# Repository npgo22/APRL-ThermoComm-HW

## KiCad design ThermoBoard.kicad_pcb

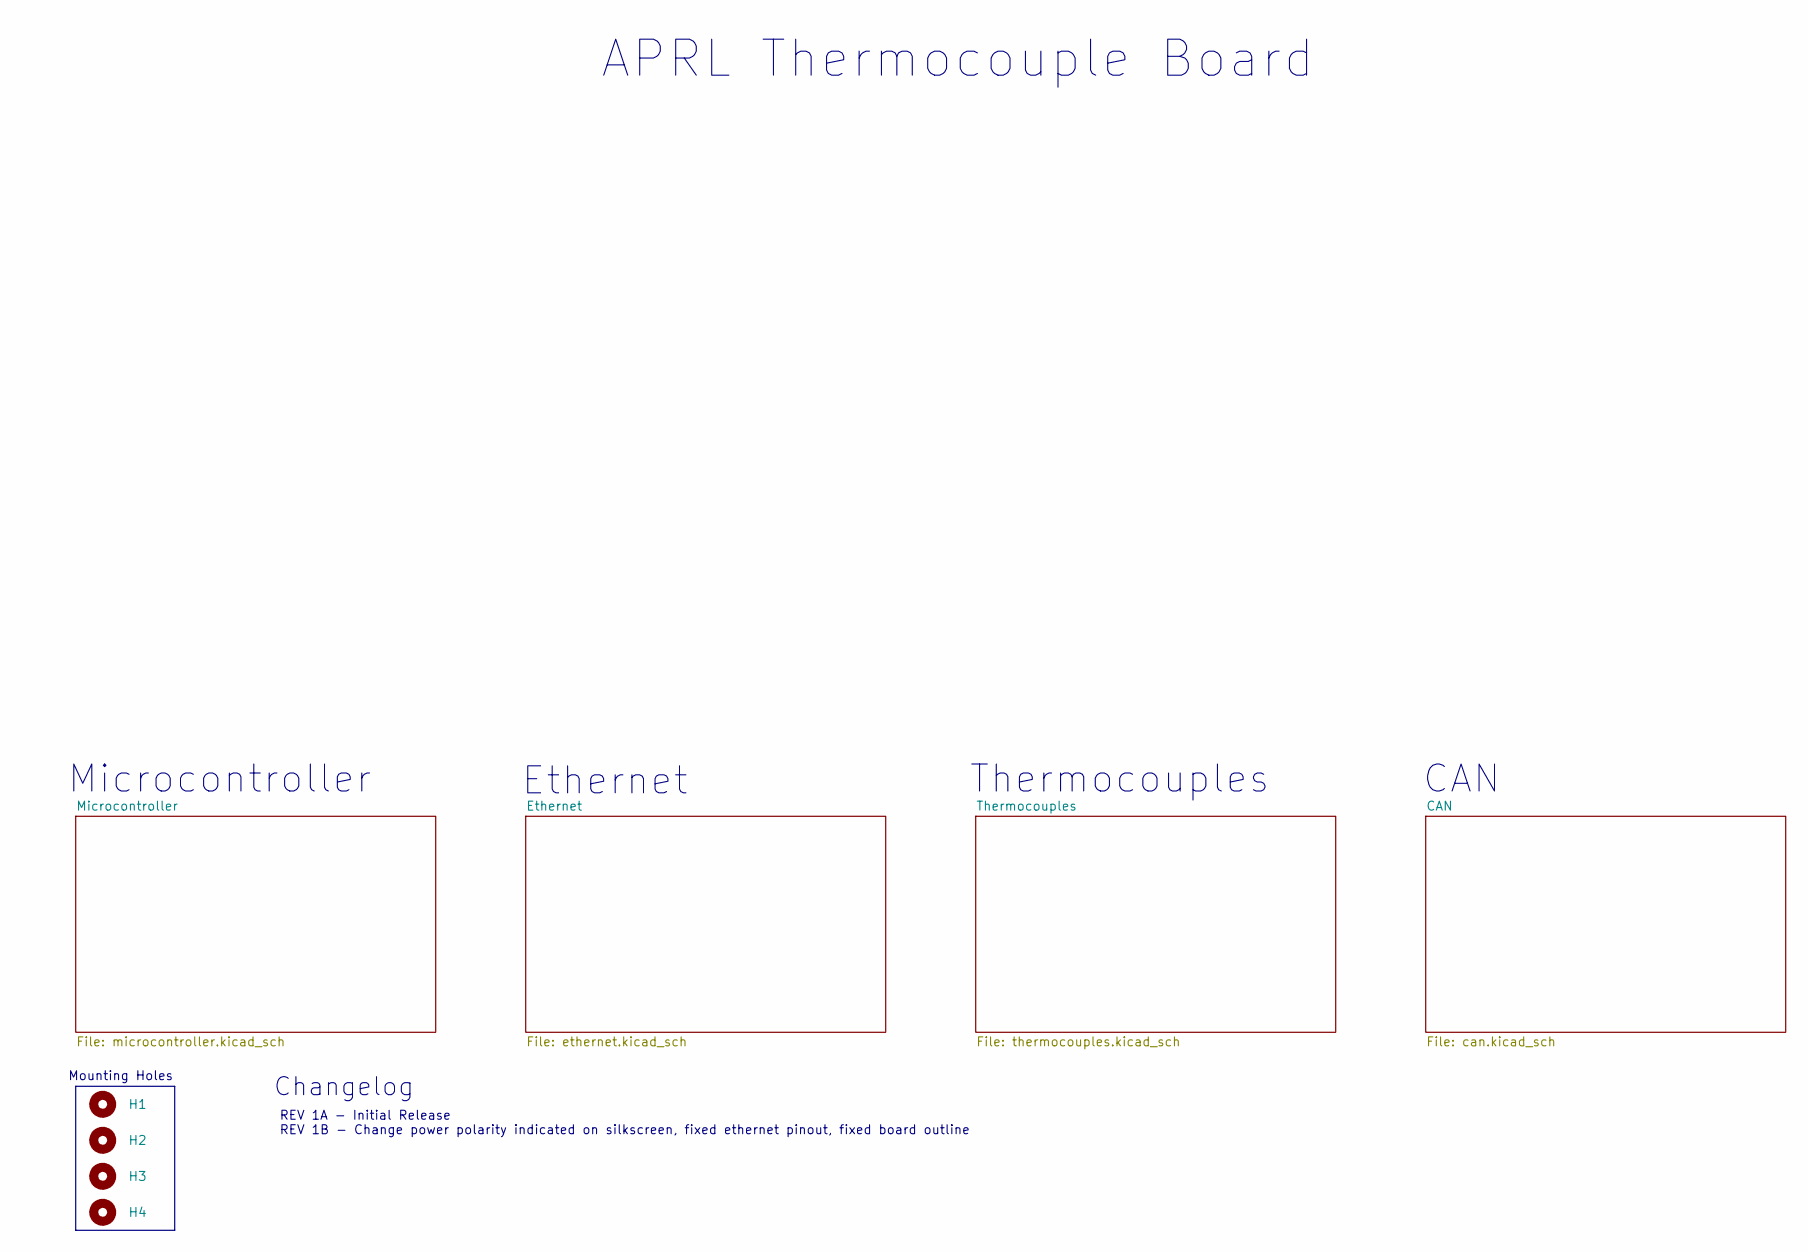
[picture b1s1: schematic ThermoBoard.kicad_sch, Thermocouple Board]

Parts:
H1, H2, H3, H4: MountingHole; MountingHole_3.2mm_M3

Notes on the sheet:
Changelog
APRL Thermocouple Board
REV 1A - Initial Release REV 1B - Change power polarity indicated on silkscreen, fixed ethernet pinout, fixed board outline
Mounting Holes
Thermocouples
Ethernet
Microcontroller
CAN

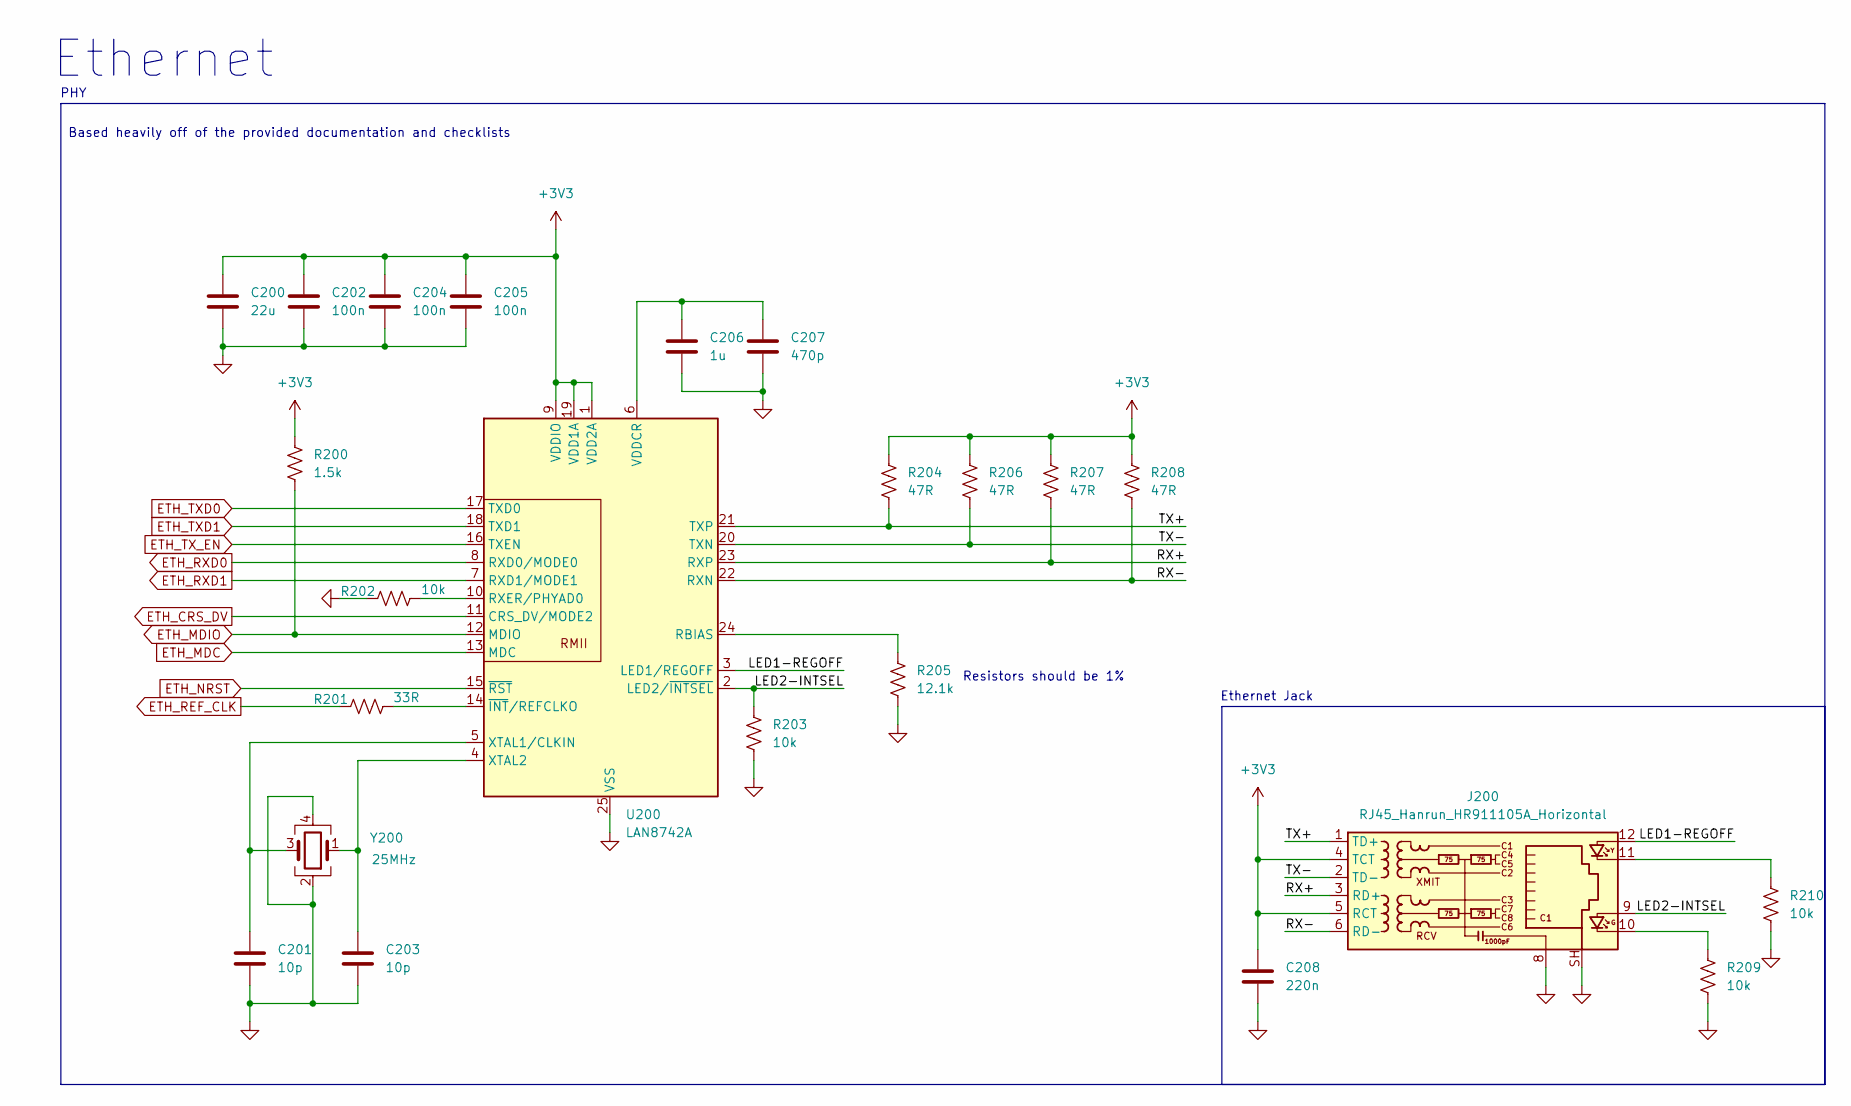
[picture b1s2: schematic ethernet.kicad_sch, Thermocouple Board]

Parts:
C200: 22u; C_0805_2012Metric; LCSC C602037
C201, C203: 10p; C_0402_1005Metric; LCSC C32949
C202, C204, C205: 100n; C_0402_1005Metric; LCSC C1525
C206: 1u; C_0402_1005Metric; LCSC C602037
C207: 470p; C_0402_1005Metric; LCSC C602037
C208: 220n; C_0402_1005Metric; LCSC C1525
J200: RJ45_Hanrun_HR911105A_Horizontal; LCSC C12074
R200: 1.5k; R_0402_1005Metric; LCSC C60490
R201: 33R; R_0402_1005Metric; LCSC C138002
R202, R203: 10k; R_0402_1005Metric; LCSC C60490
R204, R206, R207, R208: 47R; R_0402_1005Metric; LCSC C87044
R205: 12.1k; R_0402_1005Metric; LCSC C25852
R209, R210: 10k; R_0402_1005Metric; LCSC C105875
U200: LAN8742A; VQFN-24-1EP_4x4mm_P0.5mm_EP2.5x2.5mm_ThermalVias
Y200: 25MHz; CRYSTAL-SMD_4P-L2.0-W1.6-BL; LCSC C5765970

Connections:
+3V3: C200.1, C202.1, C204.1, C205.1, C208.1, J200.4 (TCT), J200.5 (RCT), R200.1, R204.1, R206.1, R207.1, R208.1, U200.1 (VDD2A), U200.9 (VDDIO), U200.19 (VDD1A); also elsewhere on the board
/Ethernet/LED1-REGOFF: J200.12, U200.3 (LED1/REGOFF)
/Ethernet/LED2-INTSEL: J200.9, R203.1, U200.2 (LED2/~INTSEL)
/Ethernet/RX+: J200.3 (RD+), R207.2, U200.23 (RXP)
/Ethernet/RX-: J200.6 (RD-), R208.2, U200.22 (RXN)
/Ethernet/TX+: J200.1 (TD+), R204.2, U200.21 (TXP)
/Ethernet/TX-: J200.2 (TD-), R206.2, U200.20 (TXN)
ETH_CRS_DV: U200.11 (CRS_DV/MODE2); also elsewhere on the board
ETH_MDC: U200.13 (MDC); also elsewhere on the board
ETH_MDIO: R200.2, U200.12 (MDIO); also elsewhere on the board
ETH_NRST: U200.15 (~RST); also elsewhere on the board
ETH_REF_CLK: R201.1; also elsewhere on the board
ETH_RXD0: U200.8 (RXD0/MODE0); also elsewhere on the board
ETH_RXD1: U200.7 (RXD1/MODE1); also elsewhere on the board
ETH_TXD0: U200.17 (TXD0); also elsewhere on the board
ETH_TXD1: U200.18 (TXD1); also elsewhere on the board
ETH_TX_EN: U200.16 (TXEN); also elsewhere on the board
GND: C200.2, C201.2, C202.2, C203.2, C204.2, C205.2, C206.2, C207.2, C208.2, J200.8, J200.SH, R202.1, R203.2, R205.2, R209.2, R210.2, U200.25 (VSS), Y200.2, Y200.4; also elsewhere on the board
unnamed: J200.10, R209.1
unnamed: J200.11, R210.1
unnamed: R205.1, U200.24 (RBIAS)
unnamed: R202.2, U200.10 (RXER/PHYAD0)
unnamed: C206.1, C207.1, U200.6 (VDDCR)
unnamed: C201.1, U200.5 (XTAL1/CLKIN), Y200.3
unnamed: C203.1, U200.4 (XTAL2), Y200.1
unnamed: R201.2, U200.14 (~INT/REFCLKO)

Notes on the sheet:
Ethernet
Resistors should be 1%
Ethernet Jack
PHY
Based heavily off of the provided documentation and checklists

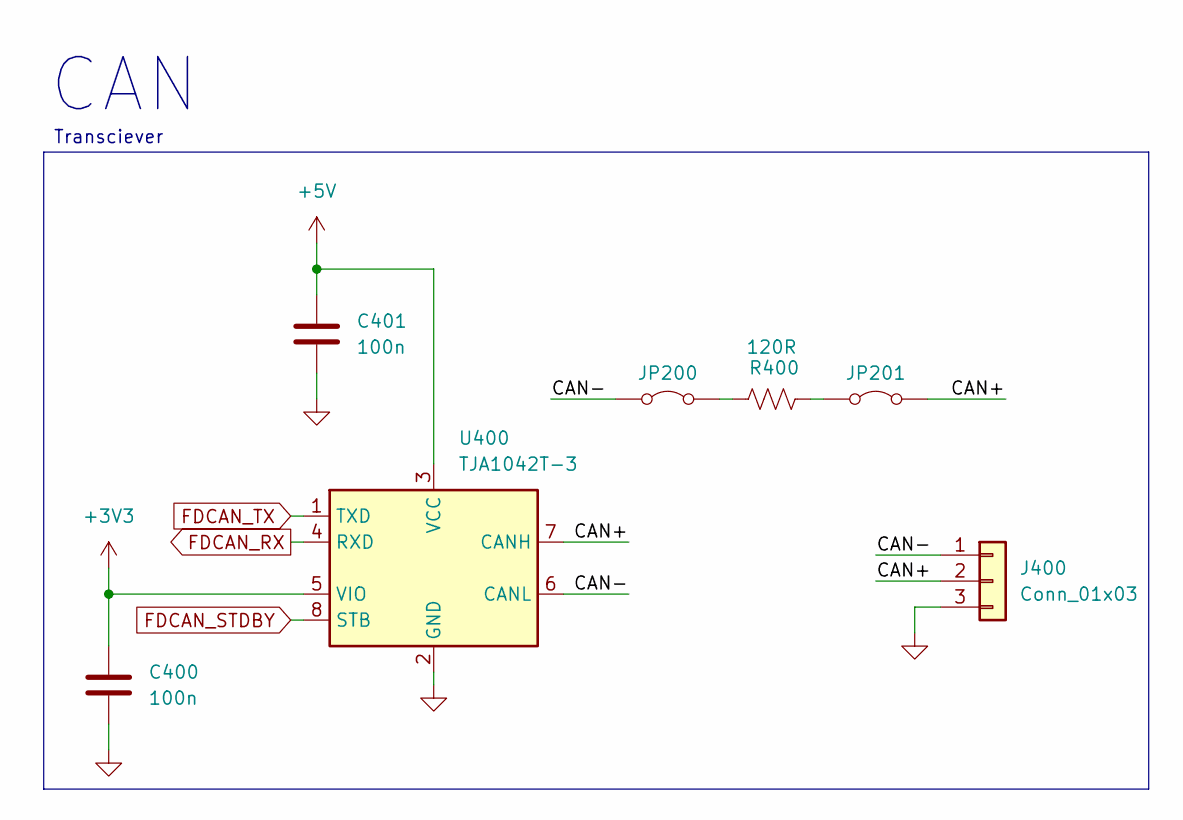
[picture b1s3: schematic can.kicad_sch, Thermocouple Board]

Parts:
C400, C401: 100n; C_0402_1005Metric; LCSC C1525
J400: Conn_01x03; PinHeader_1x03_P2.54mm_Vertical; LCSC C2337
JP200, JP201: Jumper_2_Bridged; PinHeader_1x02_P2.54mm_Vertical; LCSC C2337
R400: 120R; R_0402_1005Metric; LCSC C137954
U400: TJA1042T-3; SOIC-8_3.9x4.9mm_P1.27mm; LCSC C22445414

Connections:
+3V3: C400.1, U400.5 (VIO); also elsewhere on the board
+5V: C401.1, U400.3 (VCC); also elsewhere on the board
/CAN/CAN+: J400.2, JP201.2 (B), U400.7 (CANH)
/CAN/CAN-: J400.1, JP200.1 (A), U400.6 (CANL)
FDCAN_RX: U400.4 (RXD); also elsewhere on the board
FDCAN_STDBY: U400.8 (STB); also elsewhere on the board
FDCAN_TX: U400.1 (TXD); also elsewhere on the board
GND: C400.2, C401.2, J400.3, U400.2 (GND); also elsewhere on the board
unnamed: JP200.2 (B), R400.1
unnamed: JP201.1 (A), R400.2

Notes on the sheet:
CAN
Transciever

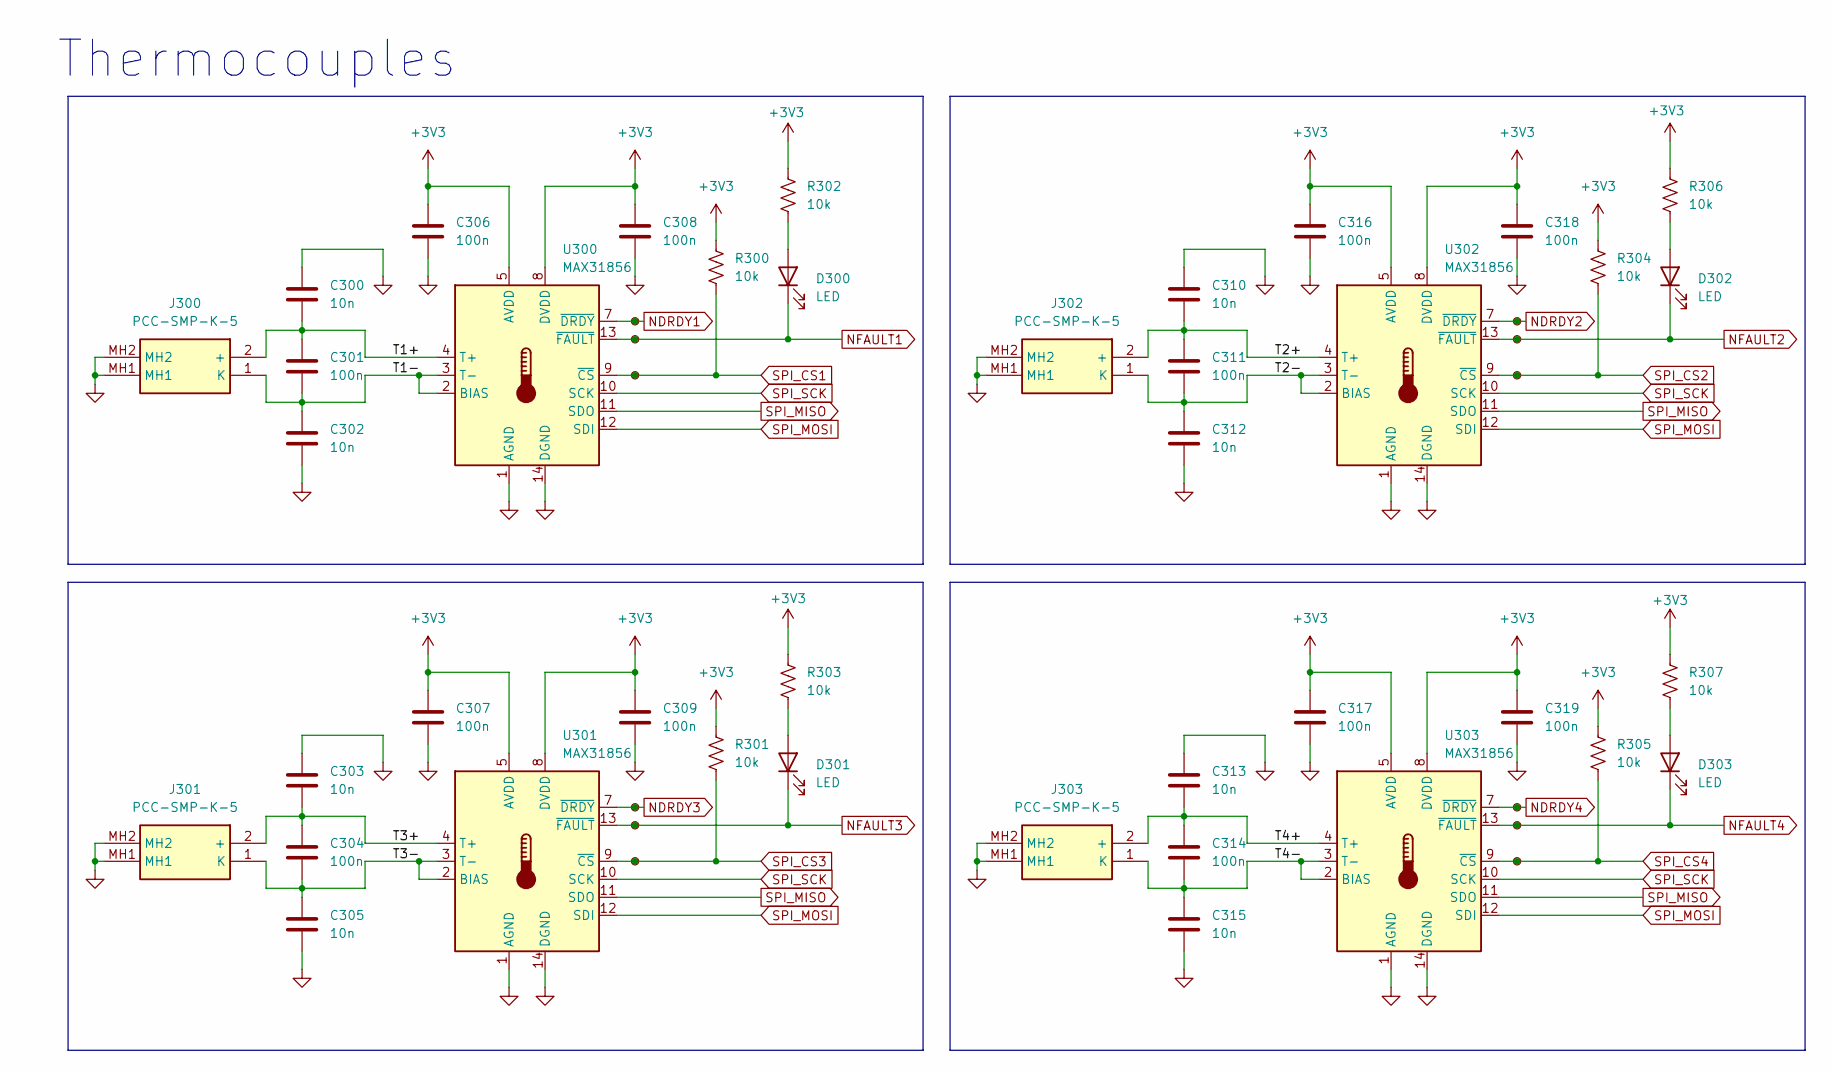
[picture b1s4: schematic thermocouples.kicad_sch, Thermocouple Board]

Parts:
C300, C302, C303, C305, C310, C312, C313, C315: 10n; C_0402_1005Metric; LCSC C15195
C301, C304, C306, C307, C308, C309, C311, C314, C316, C317, C318, C319: 100n; C_0402_1005Metric; LCSC C1525
D300, D301, D302, D303: LED; LED_0402_1005Metric; LCSC C21260817
J300, J301, J302, J303: PCC-SMP-K-5; PCCSMPK5; Manufacturer_Part_Number PCC-SMP-K-5
R300, R301, R304, R305: 10k; R_0402_1005Metric; LCSC C60490
R302, R303, R306, R307: 10k; R_0402_1005Metric; LCSC C105875
TP300, TP301, TP302, TP303, TP304, TP305, TP306, TP307, TP308, TP309, TP310, TP311: TestPoint_Small; TestPoint_Pad_D1.0mm
U300, U301, U302, U303: MAX31856; TSSOP-14_4.4x5mm_P0.65mm; LCSC C2653162

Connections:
+3V3: C306.1, C307.1, C308.1, C309.1, C316.1, C317.1, C318.1, C319.1, R300.1, R301.1, R302.1, R303.1, R304.1, R305.1, R306.1, R307.1, U300.5 (AVDD), U300.8 (DVDD), U301.5 (AVDD), U301.8 (DVDD), U302.5 (AVDD), U302.8 (DVDD), U303.5 (AVDD), U303.8 (DVDD); also elsewhere on the board
/Thermocouples/T1+: C300.2, C301.1, J300.2 (+), U300.4 (T+)
/Thermocouples/T1-: C301.2, C302.1, J300.1 (K), U300.2 (BIAS), U300.3 (T-)
/Thermocouples/T2+: C310.2, C311.1, J302.2 (+), U302.4 (T+)
/Thermocouples/T2-: C311.2, C312.1, J302.1 (K), U302.2 (BIAS), U302.3 (T-)
/Thermocouples/T3+: C303.2, C304.1, J301.2 (+), U301.4 (T+)
/Thermocouples/T3-: C304.2, C305.1, J301.1 (K), U301.2 (BIAS), U301.3 (T-)
/Thermocouples/T4+: C313.2, C314.1, J303.2 (+), U303.4 (T+)
/Thermocouples/T4-: C314.2, C315.1, J303.1 (K), U303.2 (BIAS), U303.3 (T-)
GND: C300.1, C302.2, C303.1, C305.2, C306.2, C307.2, C308.2, C309.2, C310.1, C312.2, C313.1, C315.2, C316.2, C317.2, C318.2, C319.2, J300.MH1, J300.MH2, J301.MH1, J301.MH2, J302.MH1, J302.MH2, J303.MH1, J303.MH2, U300.1 (AGND), U300.14 (DGND), U301.1 (AGND), U301.14 (DGND), U302.1 (AGND), U302.14 (DGND), U303.1 (AGND), U303.14 (DGND); also elsewhere on the board
NDRDY1: TP300.1, U300.7 (~DRDY); also elsewhere on the board
NDRDY2: TP306.1, U302.7 (~DRDY); also elsewhere on the board
NDRDY3: TP303.1, U301.7 (~DRDY); also elsewhere on the board
NDRDY4: TP309.1, U303.7 (~DRDY); also elsewhere on the board
NFAULT1: D300.1 (K), TP301.1, U300.13 (~FAULT); also elsewhere on the board
NFAULT2: D302.1 (K), TP307.1, U302.13 (~FAULT); also elsewhere on the board
NFAULT3: D301.1 (K), TP304.1, U301.13 (~FAULT); also elsewhere on the board
NFAULT4: D303.1 (K), TP310.1, U303.13 (~FAULT); also elsewhere on the board
unnamed: D300.2 (A), R302.2
unnamed: D301.2 (A), R303.2
unnamed: D302.2 (A), R306.2
unnamed: D303.2 (A), R307.2
SPI_CS1: R300.2, TP302.1, U300.9 (~CS); also elsewhere on the board
SPI_CS2: R304.2, TP308.1, U302.9 (~CS); also elsewhere on the board
SPI_CS3: R301.2, TP305.1, U301.9 (~CS); also elsewhere on the board
SPI_CS4: R305.2, TP311.1, U303.9 (~CS); also elsewhere on the board
SPI_MISO: U300.11 (SDO), U301.11 (SDO), U302.11 (SDO), U303.11 (SDO); also elsewhere on the board
SPI_MOSI: U300.12 (SDI), U301.12 (SDI), U302.12 (SDI), U303.12 (SDI); also elsewhere on the board
SPI_SCK: U300.10 (SCK), U301.10 (SCK), U302.10 (SCK), U303.10 (SCK); also elsewhere on the board

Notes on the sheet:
Thermocouples

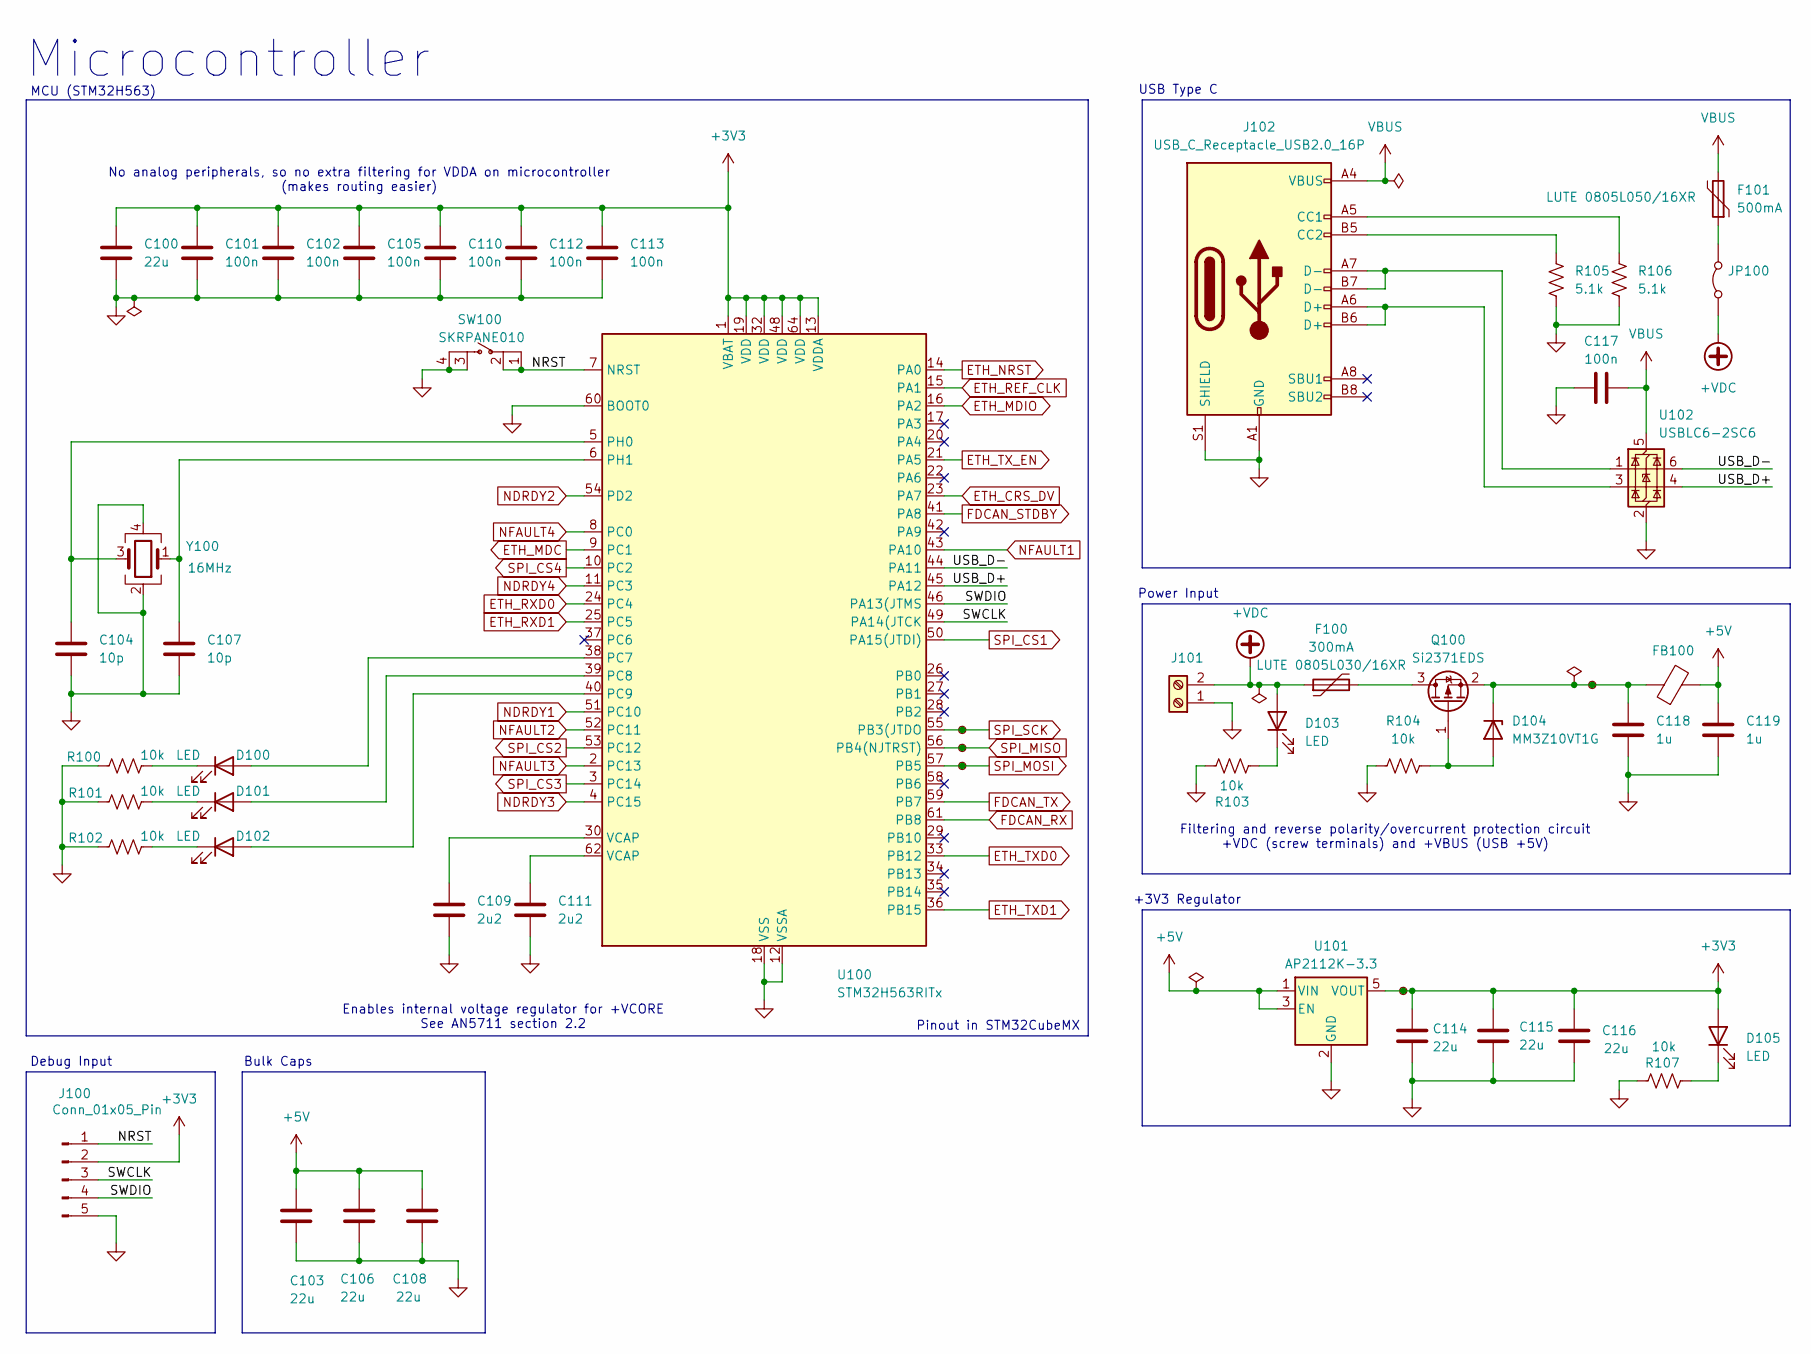
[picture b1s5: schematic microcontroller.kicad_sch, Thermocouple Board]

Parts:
C100, C103, C106, C108, C114, C115, C116: 22u; C_0805_2012Metric; LCSC C602037
C101, C102, C105, C110, C112, C113, C117: 100n; C_0402_1005Metric; LCSC C1525
C104, C107: 10p; C_0402_1005Metric; LCSC C32949
C109, C111: 2u2; C_0402_1005Metric; LCSC C170151
C118, C119: 1u; C_0402_1005Metric; LCSC C15849
D100, D101, D102, D103, D105: LED; LED_0402_1005Metric; LCSC C965793
D104: MM3Z10VT1G; SOD-323; LCSC C39057
F100: 300mA; Lute_16XR; Part LUTE 0805L030/16XR; LCSC C19193036
F101: 500mA; Lute_16XR; Part LUTE 0805L050/16XR; LCSC C22435898
FB100: FerriteBead; LSMGA160808T601RG
J100: Conn_01x05_Pin; PinHeader_1x05_P2.54mm_Vertical; LCSC C2337
J101: Screw_Terminal_01x02; TerminalBlock_Phoenix_MPT-0,5-2-2.54_1x02_P2.54mm_Horizontal; LCSC C3029316
J102: USB_C_Receptacle_USB2.0_16P; USB_C_Receptacle_HRO_TYPE-C-31-M-12; LCSC C165948
JP100: Jumper_2_Bridged; PinHeader_1x02_P2.54mm_Vertical; LCSC C2337
Q100: Si2371EDS; SOT-23; LCSC C467897
R100, R101, R102, R103, R107: 10k; R_0402_1005Metric; LCSC C105875
R104: 10k; R_0402_1005Metric; LCSC C60490
R105, R106: 5.1k; R_0402_1005Metric; LCSC C105873
SW100: SKRPANE010; SW-SMD_4P-L4.2-W3.2-P2.15-LS4.6-2; LCSC C2909692
TP100, TP101, TP102, TP104, TP105: TestPoint_Small; TestPoint_Pad_D1.0mm
U100: STM32H563RITx; LQFP-64_10x10mm_P0.5mm; LCSC C20619634
U101: AP2112K-3.3; SOT-23-5; LCSC C51118
U102: USBLC6-2SC6; SOT-23-6; LCSC C7519
Y100: 16MHz; CRYSTAL-SMD_4P-L2.0-W1.6-BL; LCSC C2901668

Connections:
+3V3: C100.1, C101.1, C102.1, C105.1, C110.1, C112.1, C113.1, C114.2, C115.2, C116.2, D105.2 (A), J100.2, TP104.1, U100.1 (VBAT), U100.13 (VDDA), U100.19 (VDD), U100.32 (VDD), U100.48 (VDD), U100.64 (VDD), U101.5 (VOUT); also elsewhere on the board
+5V: C103.2, C106.2, C108.2, C119.1, FB100.2, U101.1 (VIN), U101.3 (EN); also elsewhere on the board
+VDC: D103.2 (A), F100.1, J101.2, JP100.1 (A)
/Microcontroller/NRST: J100.1, SW100.1, SW100.2, U100.7 (NRST)
/Microcontroller/SWCLK: J100.3, U100.49 (PA14(JTCK)
/Microcontroller/SWDIO: J100.4, U100.46 (PA13(JTMS)
/Microcontroller/USB_D+: U100.45 (PA12), U102.4 (I/O2)
/Microcontroller/USB_D-: U100.44 (PA11), U102.6 (I/O1)
ETH_CRS_DV: U100.23 (PA7); also elsewhere on the board
ETH_MDC: U100.9 (PC1); also elsewhere on the board
ETH_MDIO: U100.16 (PA2); also elsewhere on the board
ETH_NRST: U100.14 (PA0); also elsewhere on the board
ETH_REF_CLK: U100.15 (PA1); also elsewhere on the board
ETH_RXD0: U100.24 (PC4); also elsewhere on the board
ETH_RXD1: U100.25 (PC5); also elsewhere on the board
ETH_TXD0: U100.33 (PB12); also elsewhere on the board
ETH_TXD1: U100.36 (PB15); also elsewhere on the board
ETH_TX_EN: U100.21 (PA5); also elsewhere on the board
FDCAN_RX: U100.61 (PB8); also elsewhere on the board
FDCAN_STDBY: U100.41 (PA8); also elsewhere on the board
FDCAN_TX: U100.59 (PB7); also elsewhere on the board
GND: C100.2, C101.2, C102.2, C103.1, C104.2, C105.2, C106.1, C107.2, C108.1, C109.2, C110.2, C111.2, C112.2, C113.2, C114.1, C115.1, C116.1, C117.1, C118.2, C119.2, J100.5, J101.1, J102.A1 (GND), J102.A12 (GND), J102.B1 (GND), J102.B12 (GND), J102.S1 (SHIELD), R100.1, R101.1, R102.1, R103.2, R104.1, R105.2, R106.2, R107.1, SW100.3, SW100.4, U100.12 (VSSA), U100.18 (VSS), U100.31 (VSS), U100.47 (VSS), U100.60 (BOOT0), U100.63 (VSS), U101.2 (GND), U102.2 (GND), Y100.2, Y100.4; also elsewhere on the board
NDRDY1: U100.51 (PC10); also elsewhere on the board
NDRDY2: U100.54 (PD2); also elsewhere on the board
NDRDY3: U100.4 (PC15); also elsewhere on the board
NDRDY4: U100.11 (PC3); also elsewhere on the board
NFAULT1: U100.43 (PA10); also elsewhere on the board
NFAULT2: U100.52 (PC11); also elsewhere on the board
NFAULT3: U100.2 (PC13); also elsewhere on the board
NFAULT4: U100.8 (PC0); also elsewhere on the board
unnamed: C109.1, U100.30 (VCAP)
unnamed: C111.1, U100.62 (VCAP)
unnamed: D100.2 (A), U100.38 (PC7)
unnamed: D100.1 (K), R100.2
unnamed: D101.2 (A), U100.39 (PC8)
unnamed: D101.1 (K), R101.2
unnamed: D102.2 (A), U100.40 (PC9)
unnamed: D102.1 (K), R102.2
unnamed: D103.1 (K), R103.1
unnamed: D104.2 (A), Q100.1 (G), R104.2
unnamed: C118.1, D104.1 (K), FB100.1, Q100.2 (S), TP105.1
unnamed: D105.1 (K), R107.2
unnamed: J102.A5 (CC1), R106.1
unnamed: J102.B5 (CC2), R105.1
unnamed: J102.A6 (D+), J102.B6 (D+), U102.3 (I/O2)
unnamed: J102.A7 (D-), J102.B7 (D-), U102.1 (I/O1)
unnamed: F101.1, JP100.2 (B)
unnamed: F100.2, Q100.3 (D)
unnamed: C104.1, U100.5 (PH0), Y100.3
unnamed: C107.1, U100.6 (PH1), Y100.1
SPI_CS1: U100.50 (PA15(JTDI)); also elsewhere on the board
SPI_CS2: U100.53 (PC12); also elsewhere on the board
SPI_CS3: U100.3 (PC14); also elsewhere on the board
SPI_CS4: U100.10 (PC2); also elsewhere on the board
SPI_MISO: TP101.1, U100.56 (PB4(NJTRST)); also elsewhere on the board
SPI_MOSI: TP102.1, U100.57 (PB5); also elsewhere on the board
SPI_SCK: TP100.1, U100.55 (PB3(JTDO); also elsewhere on the board
VBUS: C117.2, F101.2, J102.A4 (VBUS), J102.A9 (VBUS), J102.B4 (VBUS), J102.B9 (VBUS), U102.5 (VBUS)

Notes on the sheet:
Microcontroller
Debug Input
Power Input
+3V3 Regulator
Pinout in STM32CubeMX
Enables internal voltage regulator for +VCORE See AN5711 section 2.2
No analog peripherals, so no extra filtering for VDDA on microcontroller (makes routing easier)
Bulk Caps
Filtering and reverse polarity/overcurrent protection circuit +VDC (screw terminals) and +VBUS (USB +5V)
USB Type C
MCU (STM32H563)

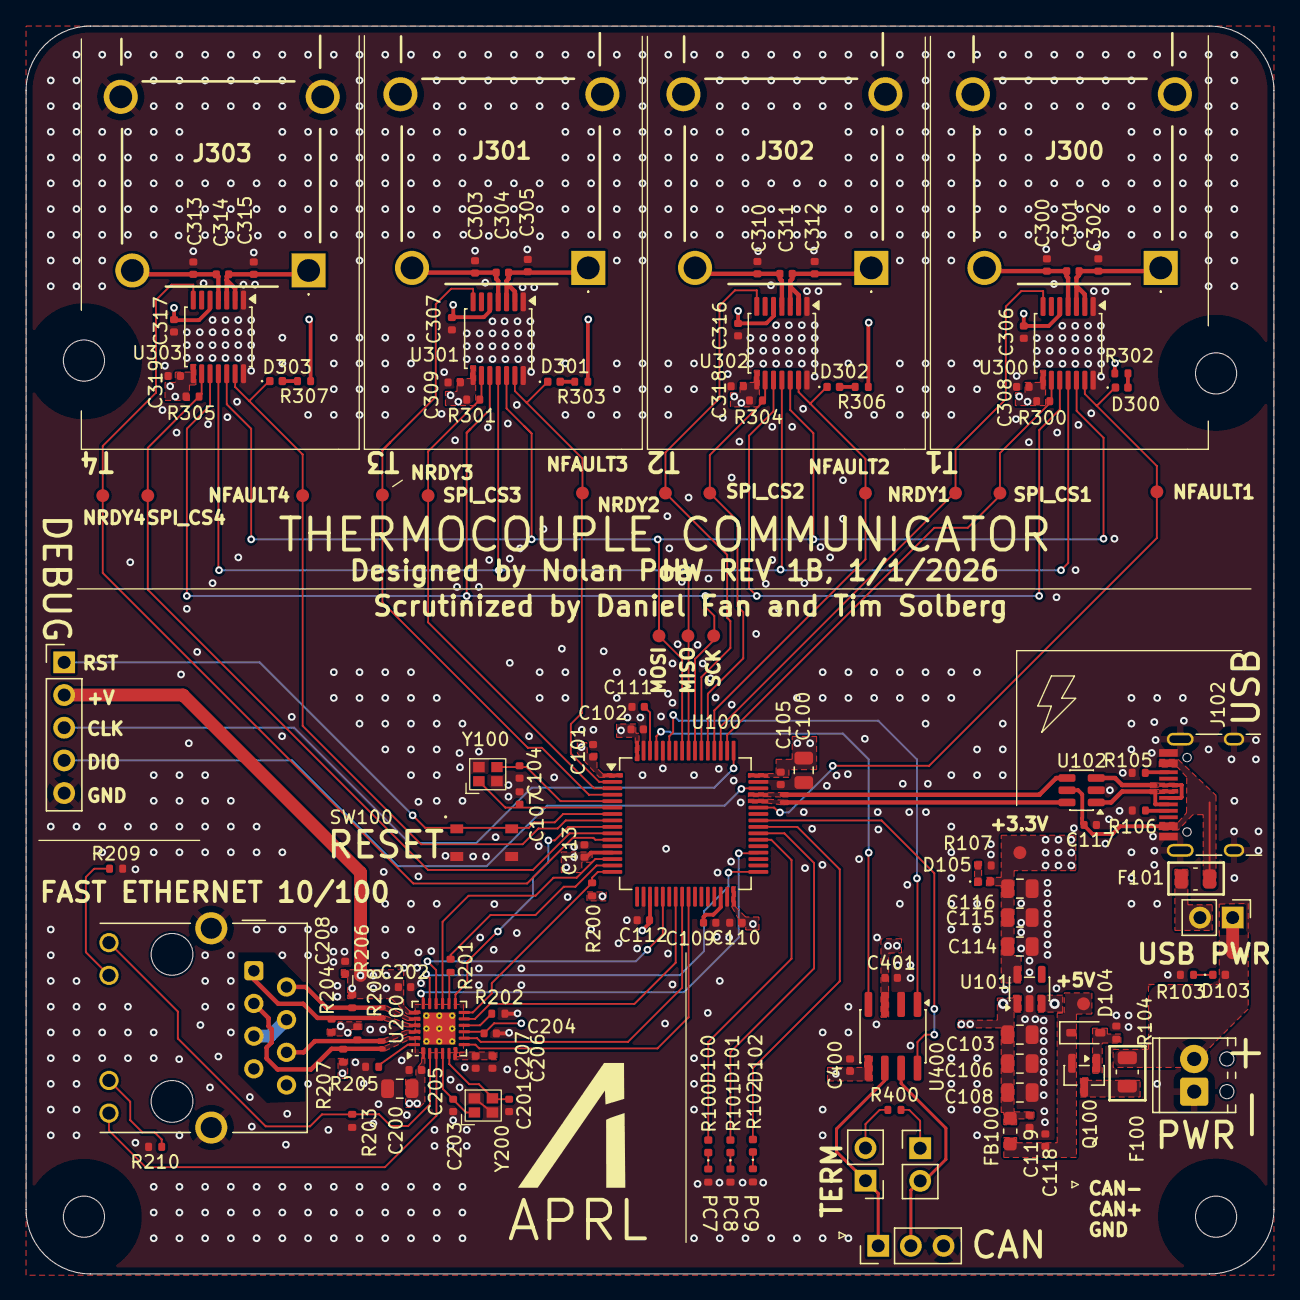
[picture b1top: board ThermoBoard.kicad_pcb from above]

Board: 4 copper layers, 97.0 x 97.0 mm, 138 parts (0 on the bottom side), 88 nets.

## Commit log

2025-10-16 feat: First public release
2025-10-16 feat: release
2025-10-16 fix: Silkscreen overlaps
2025-10-16 chore: Prep for release
2025-10-16 fix: Add paste
2026-01-01 Rev 1B - Fix silkscreen, board outline, ethernet pinout
2026-01-01 fix DRC Problems
2026-06-29 Add renovate.json
